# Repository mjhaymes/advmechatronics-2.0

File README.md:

# ME 499 - Advanced Mechatronics 2.0
In this project I'll be doing some signal processing, PCB design, control circuitry, and embedded computing with a PIC32 microprocessor. More to come.

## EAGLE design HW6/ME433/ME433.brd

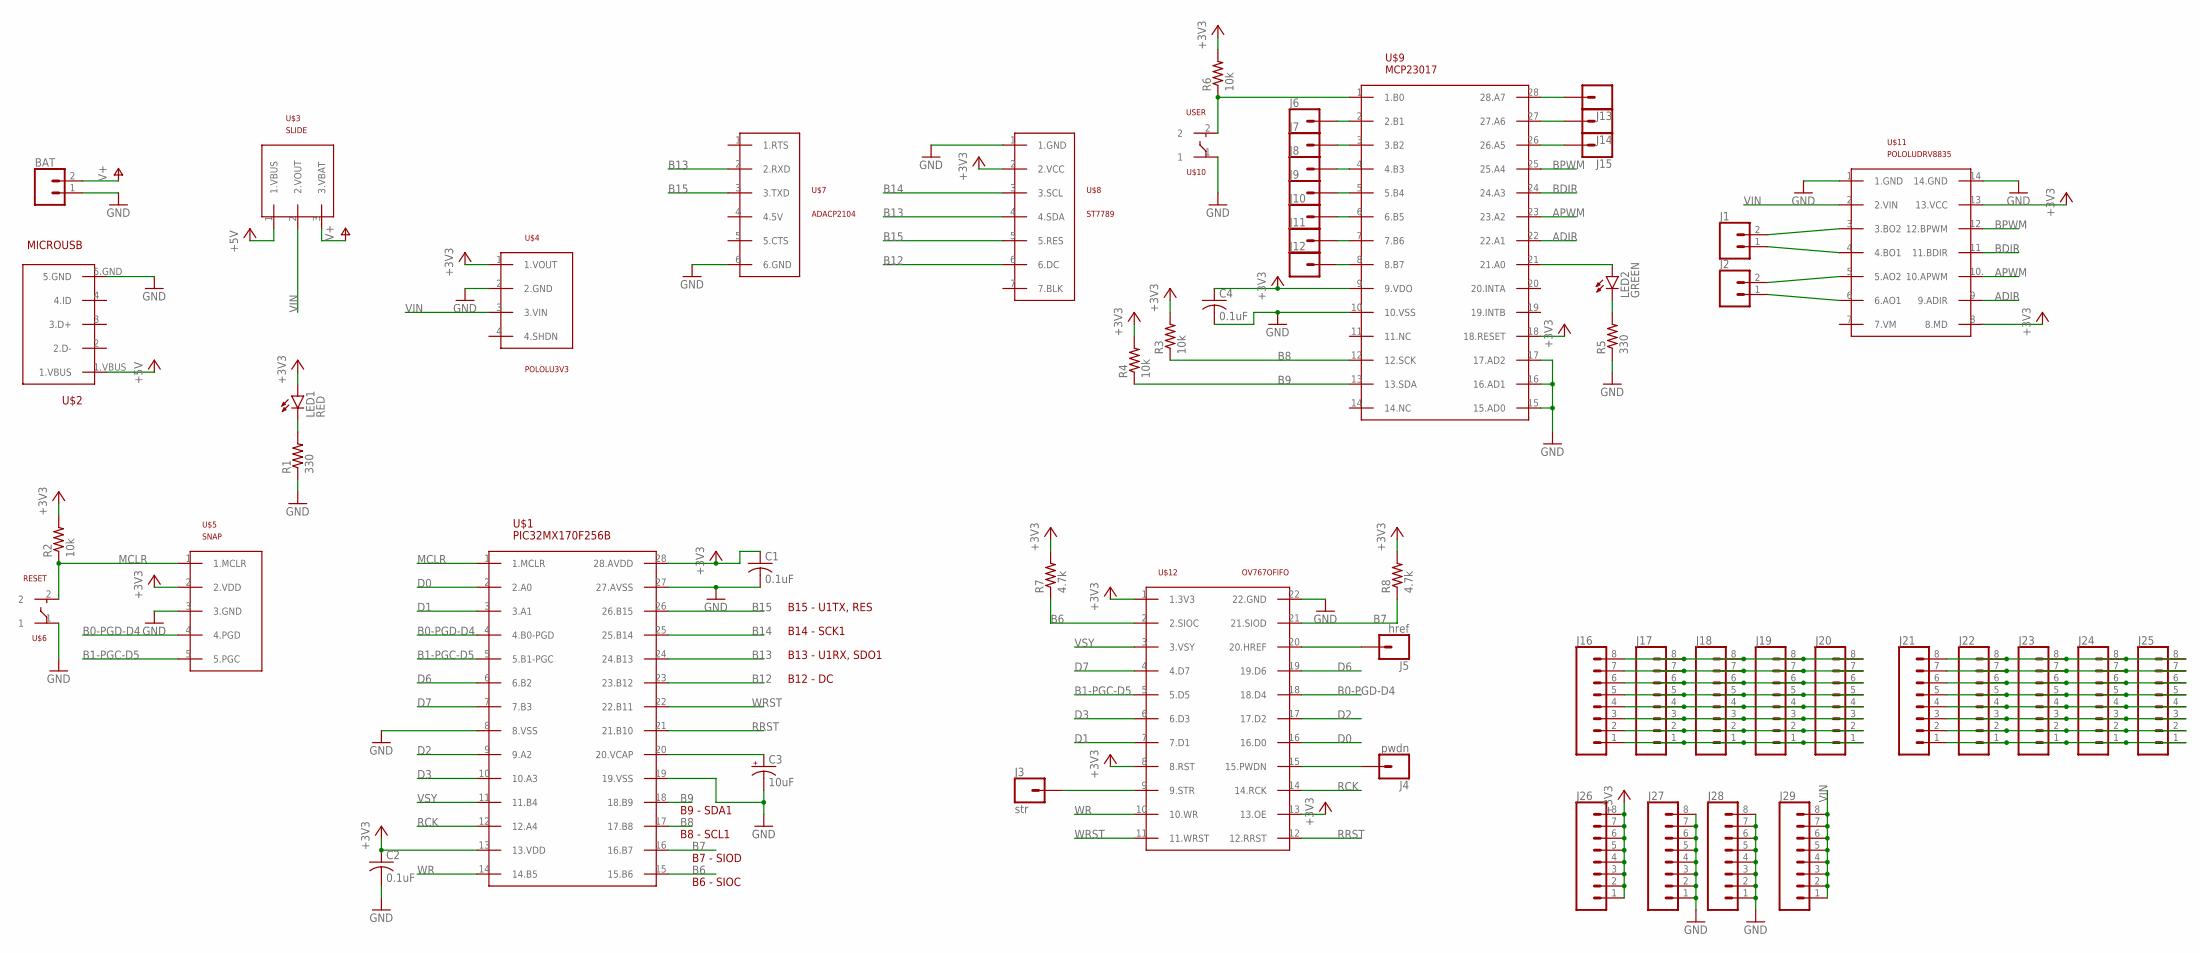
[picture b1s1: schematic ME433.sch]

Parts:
BAT: CONN_02; 1X02
C1, C2, C4: 0.1uF; C025-030X050
C3: 10uF; B45181B
J1, J2: CONN_02; 1X02
J3: str; 1X01
J4: pwdn; 1X01
J5: href; 1X01
J6, J7, J8, J9, J10, J11, J12, J13, J14, J15: CONN_01; 1X01
J16, J17, J18, J19, J20, J21, J22, J23, J24, J25, J26, J27, J28, J29: CONN_08"; 1X08
LED1: RED; LED3MM
LED2: GREEN; LED3MM
R1, R5: 330; 0207/10
R2, R3, R4, R6: 10k; 0207/10
R7, R8: 4.7k; 0207/10
U$1: PIC32MX170F256B; DIL28-3
U$2: MICROUSB
U$3: SLIDE
U$4: POLOLU3V3
U$5: SNAP
U$6: RESET; PUSH
U$7: ADACP2104
U$8: ST7789
U$9: MCP23017
U$10: USER; PUSH
U$11: POLOLUDRV8835
U$12: OV767OFIFO

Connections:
+3V3: C1.1, C2.1, C4.1, J26.1, J26.2, J26.3, J26.4, J26.5, J26.6, J26.7, J26.8, LED1.A, R2.2, R3.2, R4.2, R6.2, R7.2, R8.2, U$1.13 (13.VDD), U$1.28 (28.AVDD), U$4.1 (1.VOUT), U$5.2 (2.VDD), U$8.2 (2.VCC), U$9.9 (9.VDO), U$9.18 (18.RESET), U$11.8 (8.MD), U$11.13 (13.VCC), U$12.1 (1.3V3), U$12.8 (8.RST), U$12.13 (13.OE)
+5V: U$2.1.VBUS, U$3.1 (1.VBUS)
ADIR: U$9.22 (22.A1), U$11.9 (9.ADIR)
APWM: U$9.23 (23.A2), U$11.10. (10.APWM)
B0-PGD-D4: U$1.4 (4.B0-PGD), U$5.4 (4.PGD), U$12.18 (18.D4)
B1-PGC-D5: U$1.5 (5.B1-PGC), U$5.5 (5.PGC), U$12.5 (5.D5)
B6: R7.1, U$1.15 (15.B6), U$12.2 (2.SIOC)
B7: R8.1, U$1.16 (16.B7), U$12.21 (21.SIOD)
B8: R3.1, U$1.17 (17.B8), U$9.12 (12.SCK)
B9: R4.1, U$1.18 (18.B9), U$9.13 (13.SDA)
B12: U$1.23 (23.B12), U$8.6 (6.DC)
B13: U$1.24 (24.B13), U$7.2 (2.RXD), U$8.4 (4.SDA)
B14: U$1.25 (25.B14), U$8.3 (3.SCL)
B15: U$1.26 (26.B15), U$7.3 (3.TXD), U$8.5 (5.RES)
BDIR: U$9.24 (24.A3), U$11.11 (11.BDIR)
BPWM: U$9.25 (25.A4), U$11.12 (12.BPWM)
D0: U$1.2 (2.A0), U$12.16 (16.D0)
D1: U$1.3 (3.A1), U$12.7 (7.D1)
D2: U$1.9 (9.A2), U$12.17 (17.D2)
D3: U$1.10 (10.A3), U$12.6 (6.D3)
D6: U$1.6 (6.B2), U$12.19 (19.D6)
D7: U$1.7 (7.B3), U$12.4 (4.D7)
GND: BAT.1, C1.2, C2.2, C3.-, C4.2, J27.1, J27.2, J27.3, J27.4, J27.5, J27.6, J27.7, J27.8, J28.1, J28.2, J28.3, J28.4, J28.5, J28.6, J28.7, J28.8, R1.1, R5.1, U$1.8 (8.VSS), U$1.19 (19.VSS), U$1.27 (27.AVSS), U$2.5.GND, U$4.2 (2.GND), U$5.3 (3.GND), U$6.1, U$7.6 (6.GND), U$8.1 (1.GND), U$9.10 (10.VSS), U$9.15 (15.AD0), U$9.16 (16.AD1), U$9.17 (17.AD2), U$10.1, U$11.1 (1.GND), U$11.14 (14.GND), U$12.22 (22.GND)
MCLR: R2.1, U$1.1 (1.MCLR), U$5.1 (1.MCLR), U$6.2
unnamed: LED1.K (C), R1.2
unnamed: C3.+, U$1.20 (20.VCAP)
unnamed: LED2.A, U$9.21 (21.A0)
unnamed: LED2.K (C), R5.2
unnamed: R6.1, U$9.1 (1.B0), U$10.2
unnamed: J1.2, U$11.3 (3.BO2)
unnamed: J1.1, U$11.4 (4.BO1)
unnamed: J2.2, U$11.5 (5.AO2)
unnamed: J2.1, U$11.6 (6.AO1)
unnamed: J3.1, U$12.9 (9.STR)
unnamed: J4.1, U$12.15 (15.PWDN)
unnamed: J5.1, U$12.20 (20.HREF)
unnamed: J6.1, U$9.2 (2.B1)
unnamed: J7.1, U$9.3 (3.B2)
unnamed: J8.1, U$9.4 (4.B3)
unnamed: J9.1, U$9.5 (5.B4)
unnamed: J10.1, U$9.6 (6.B5)
unnamed: J11.1, U$9.7 (7.B6)
unnamed: J12.1, U$9.8 (8.B7)
unnamed: J13.1, U$9.28 (28.A7)
unnamed: J14.1, U$9.27 (27.A6)
unnamed: J15.1, U$9.26 (26.A5)
unnamed: J16.8, J17.8, J18.8, J19.8, J20.8
unnamed: J16.7, J17.7, J18.7, J19.7, J20.7
unnamed: J16.6, J17.6, J18.6, J19.6, J20.6
unnamed: J16.5, J17.5, J18.5, J19.5, J20.5
unnamed: J16.4, J17.4, J18.4, J19.4, J20.4
unnamed: J16.3, J17.3, J18.3, J19.3, J20.3
unnamed: J16.2, J17.2, J18.2, J19.2, J20.2
unnamed: J16.1, J17.1, J18.1, J19.1, J20.1
unnamed: J21.8, J22.8, J23.8, J24.8, J25.8
unnamed: J21.7, J22.7, J23.7, J24.7, J25.7
unnamed: J21.6, J22.6, J23.6, J24.6, J25.6
unnamed: J21.5, J22.5, J23.5, J24.5, J25.5
unnamed: J21.4, J22.4, J23.4, J24.4, J25.4
unnamed: J21.3, J22.3, J23.3, J24.3, J25.3
unnamed: J21.2, J22.2, J23.2, J24.2, J25.2
unnamed: J21.1, J22.1, J23.1, J24.1, J25.1
RCK: U$1.12 (12.A4), U$12.14 (14.RCK)
RRST: U$1.21 (21.B10), U$12.12 (12.RRST)
V+: BAT.2, U$3.3 (3.VBAT)
VIN: J29.1, J29.2, J29.3, J29.4, J29.5, J29.6, J29.7, J29.8, U$3.2 (2.VOUT), U$4.3 (3.VIN), U$11.2 (2.VIN)
VSY: U$1.11 (11.B4), U$12.3 (3.VSY)
WR: U$1.14 (14.B5), U$12.10 (10.WR)
WRST: U$1.22 (22.B11), U$12.11 (11.WRST)

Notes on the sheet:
B15 - U1TX, RES
B13 - U1RX, SDO1
B12 - DC
B14 - SCK1
B9 - SDA1
B8 - SCL1
B7 - SIOD
B6 - SIOC

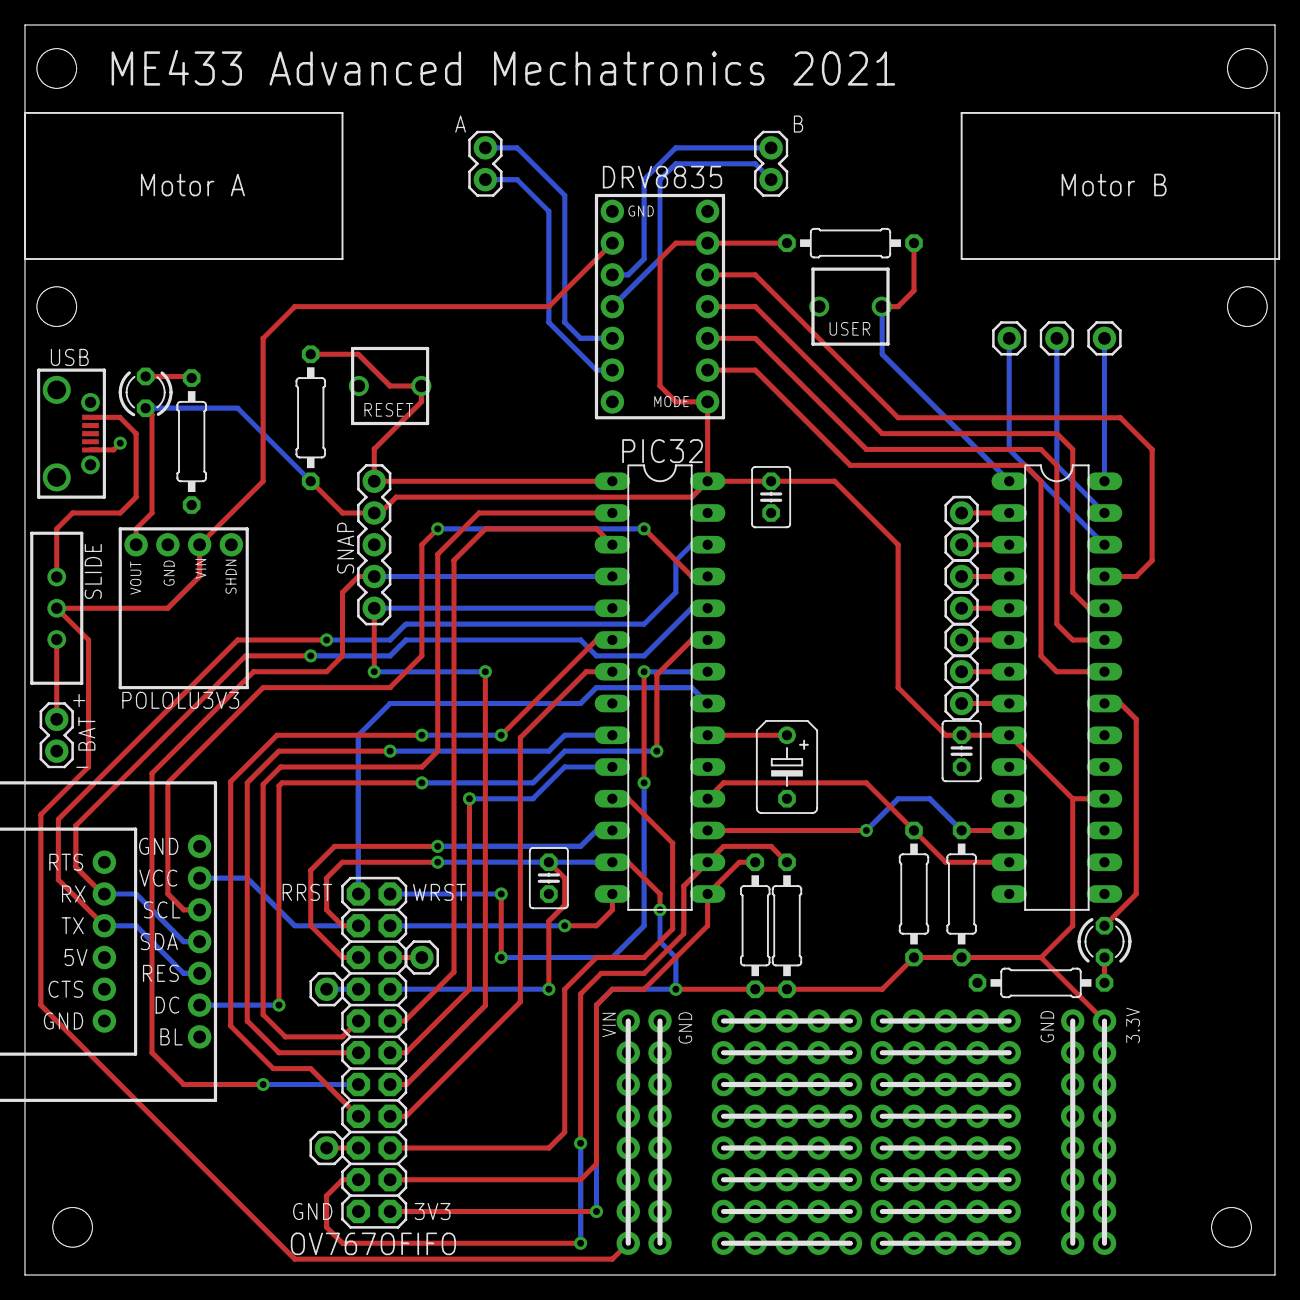
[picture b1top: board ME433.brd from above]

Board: 2 copper layers, 100.0 x 100.0 mm, 56 parts (0 on the bottom side), 69 nets.

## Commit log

2021-04-11 Uploading code and figures
    Code is under sigproc.py, csv files are included, and figures included via their respective names
2021-04-18 Adding Folders
2021-04-18 added picture of lab kit
2021-04-18 Adding HW4
    Added the code, the circuit/circuit diagram, and a demo of the blinking LED
2021-04-28 submission of HW5
2021-04-28 switching some folders around
2021-04-30 Upload of Hw7 stuff
2021-04-30 upload of hw7 and hw8 materials
2021-05-06 uploading all the files for hw6
2021-05-09 upload of neopixel code
    HW10
2021-05-16 hw stuff
    idk lots a stuff im tired
2021-06-12 upload of hw16
